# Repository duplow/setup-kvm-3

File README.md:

# setup-kvm-3

**Chaveador KVM** (**K**eyboard **V**ideo **M**ouse) para até 3 PCs/aparelhos diferentes conectados simultaneamente, podendo alternar entre sí.

_Imagem ilustrativa_

Cada aparelho conectado contará com 3 entradas **HDMI**, 3 entradas **DisplayPort** e 1 entrada **USB 3.0**.

O projeto é montado em cima de um Arduino para fazer o chaveamento entre os aparelhos via teclado, caso opte por um chaveamento apenas via botão fisico o Arduino não será necessário.

O chavemento será feito pelo botão físico no aparelho ou via um teclado USB usando os atalhos:

- `CTRL+SHIFT+NUM+1` para o aparelho número 1
- `CTRL+SHIFT+NUM+2` para o aparelho número 2
- `CTRL+SHIFT+NUM+3` para o aparelho número 3

e assim por diante

---

## Instruções

### Fabricação

 - espessura minima das trilhas (width): 0.2mm
 - espaçamento minimo (min clearance): 0.2mm (usado 0.25m)
 - fotolito: 10.000 DPI

### Módulos

- [Módulo Alimentação](/docs/power-module.md)
- [Módulo Displayport](/docs/displayport-module.md)
- [Módulo USB 3.0 tipo A](/docs/usb-30-module.md)
- [Módulo Controle](/docs/controller-module.md)

### Materiais

Componentes necessários para um KVM de até 3 aparelhos:

- **Arduino** qualquer modelo (opcional)
- 70x Buffers **SN74HC541N** (6 por HDMI, 6 por DisplayPort e 2 por USB)
- 4x Conectores **USB 3.0 DIP** fêmea
- 9x Conectores **HDMI** fêmea [link de venda](https://pt.aliexpress.com/item/1005004321901753.html?spm=a2g0o.productlist.main.3.2f4c4bd4zNbfgg&algo_pvid=e8ba0e93-4177-44cf-a99c-585d2ebb48c4&aem_p4p_detail=202302081917461309186084719520000121513&algo_exp_id=e8ba0e93-4177-44cf-a99c-585d2ebb48c4-1&pdp_ext_f=%7B%22sku_id%22%3A%2212000028751193682%22%7D&pdp_npi=3%40dis%21BRL%2118.99%2116.71%21%21%21%21%21%40211bf48d16759126661676453d06b6%2112000028751193682%21sea%21BR%214164761864&curPageLogUid=yP8cfGhjvAHO&ad_pvid=202302081917461309186084719520000121513_2&ad_pvid=202302081917461309186084719520000121513_2)
- 9x Conectores **DisplayPort DIP** fêmea
- 4x Conectores **P2** de áudio e microfone [link de venda](https://pt.aliexpress.com/item/1005004688929020.html?spm=a2g0o.ppclist.product.16.73faLsI4LsI4iQ&pdp_npi=2%40dis%21BRL%21R%24%205%2C92%21R%24%205%2C92%21%21%21%21%21%402101f6b316766497700243772e69af%2112000030107125153%21btf&_t=pvid%3Ad92d09f6-7fa5-46f7-80e0-bc18aa72a762&afTraceInfo=1005004688929020__pc__pcBridgePPC__xxxxxx__1676649770&gatewayAdapt=glo2bra)

> É possível substituir os buffers `SN74HC541N` por multiplexadores `74HC4052`, porém será necessário muitos deles para fazer o mesmo trabalho, para cada `SN74HC541N` será necessário mais ou menos 4 multiplexadores `74HC4052`.

TODO: Colocar o link para o BOM

### Esquemas

Placa USB

### Montagem

Em desenvolvimento

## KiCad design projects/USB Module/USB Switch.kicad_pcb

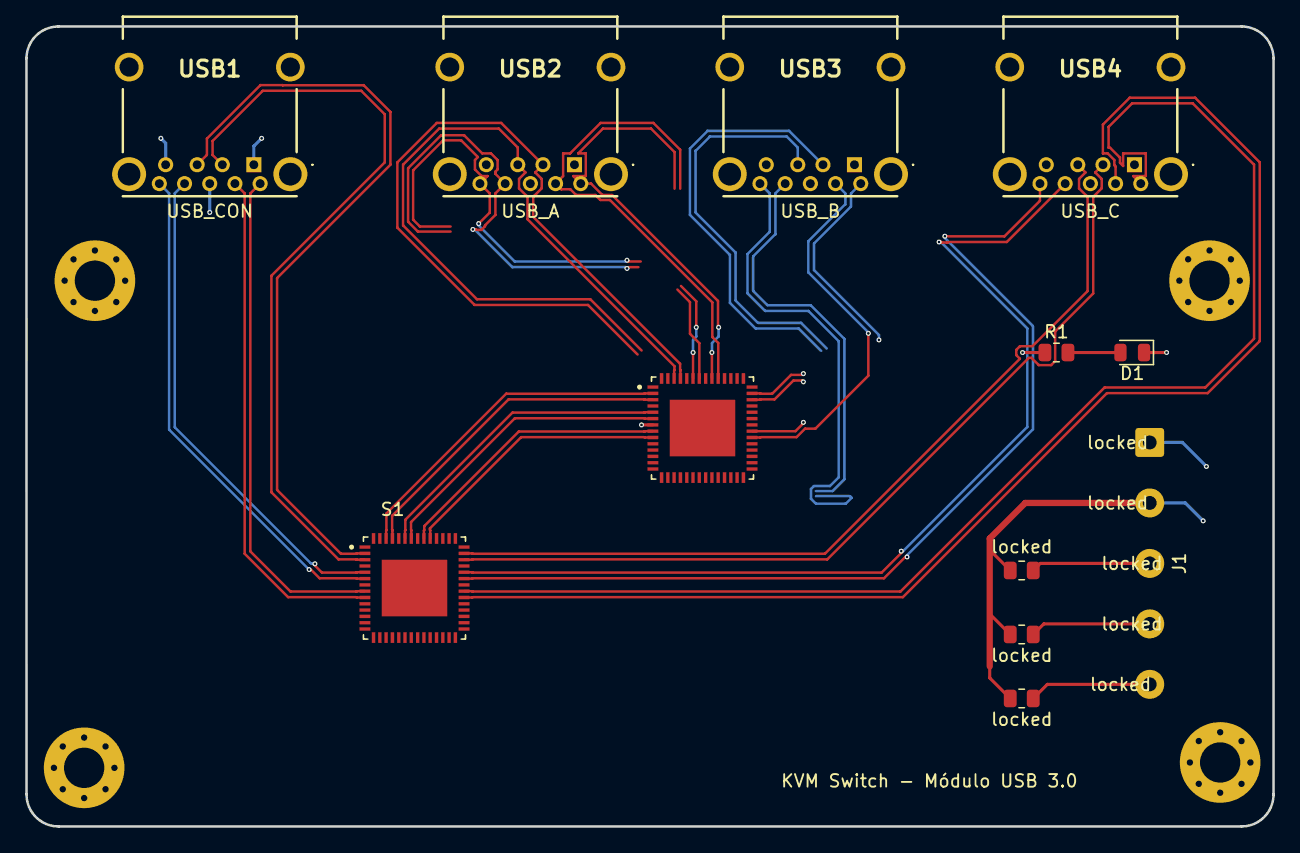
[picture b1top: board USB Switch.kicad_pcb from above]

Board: 4 copper layers, 99.0 x 63.5 mm, 12 parts (0 on the bottom side), 38 nets.

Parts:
D1: LED; LED_0805_2012Metric
J1: Conn_01x05_Socket; SolderWire-0.5sqmm_1x05_P4.8mm_D0.9mm_OD2.3mm
R1: 167R; R_0805_2012Metric
S1, S2: HD3SS215IRTQR; QFN50P800X800X100-57N
USB1, USB2, USB3, USB4: USB3_Molex_48393-0003
locked: locked; R_0805_2012Metric
locked#2, locked#3: locked; R_0805_2012Metric

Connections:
/+5V: J1.1, R1.1
/CLOCK: J1.5, locked#2.1
/GND: D1.1 (K), J1.2, locked.2, locked#2.2, locked#3.2
/S0: J1.3, S2.1 (AUX_SEL), S2.56 (DX_SEL), locked#3.1
/S1: J1.4, S1.1 (AUX_SEL), S1.56 (DX_SEL), locked.1
/Switch/+5V: S1.19 (VDD0), S1.43 (OE), S1.55 (VDD1), S2.19 (VDD0), S2.43 (OE), S2.55 (VDD1), USB1.1 (VBUS)
/Switch/D0+: S1.2 (D0_C+), USB1.3 (D+)
/Switch/D0-: S1.3 (D0_C-), USB1.2 (D-)
/Switch/D1+: S1.5 (D1_C+), USB1.6 (SSRX+)
/Switch/D1-: S1.6 (D1_C-), USB1.5 (SSRX-)
/Switch/D2+: S1.8 (D2_C+), USB1.9 (SSTX+)
/Switch/D2-: S1.9 (D2_C-), USB1.8 (SSTX-)
/Switch/USB_AB_D0+: S1.54 (D0_A+), S2.2 (D0_C+)
/Switch/USB_AB_D0-: S1.53 (D0_A-), S2.3 (D0_C-)
/Switch/USB_AB_D1+: S1.51 (D1_A+), S2.5 (D1_C+)
/Switch/USB_AB_D1-: S1.50 (D1_A-), S2.6 (D1_C-)
/Switch/USB_AB_D2+: S1.48 (D2_A+), S2.8 (D2_C+)
/Switch/USB_AB_D2-: S1.47 (D2_A-), S2.9 (D2_C-)
/Switch/USB_A_D0+: S2.54 (D0_A+), USB2.3 (D+)
/Switch/USB_A_D0-: S2.53 (D0_A-), USB2.2 (D-)
/Switch/USB_A_D1+: S2.51 (D1_A+), USB2.6 (SSRX+)
/Switch/USB_A_D1-: S2.50 (D1_A-), USB2.5 (SSRX-)
/Switch/USB_A_D2+: S2.48 (D2_A+), USB2.9 (SSTX+)
/Switch/USB_A_D2-: S2.47 (D2_A-), USB2.8 (SSTX-)
/Switch/USB_B_D0+: S2.41 (D0_B+), USB3.3 (D+)
/Switch/USB_B_D0-: S2.40 (D0_B-), USB3.2 (D-)
/Switch/USB_B_D1+: S2.38 (D1_B+), USB3.6 (SSRX+)
/Switch/USB_B_D1-: S2.37 (D1_B-), USB3.5 (SSRX-)
/Switch/USB_B_D2+: S2.35 (D2_B+), USB3.9 (SSTX+)
/Switch/USB_B_D2-: S2.34 (D2_B-), USB3.8 (SSTX-)
/Switch/USB_C_D0+: S1.41 (D0_B+), USB4.3 (D+)
/Switch/USB_C_D0-: S1.40 (D0_B-), USB4.2 (D-)
/Switch/USB_C_D1+: S1.38 (D1_B+), USB4.6 (SSRX+)
/Switch/USB_C_D1-: S1.37 (D1_B-), USB4.5 (SSRX-)
/Switch/USB_C_D2+: S1.35 (D2_B+), USB4.9 (SSTX+)
/Switch/USB_C_D2-: S1.34 (D2_B-), USB4.8 (SSTX-)
GND: S1.4 (GND0), S1.7 (GND1), S1.10 (GND2), S1.33 (GND3), S1.36 (GND4), S1.39 (GND5), S1.46 (GND6), S1.49 (GND7), S1.52 (GND8), S1.57 (PAD), S2.4 (GND0), S2.7 (GND1), S2.10 (GND2), S2.33 (GND3), S2.36 (GND4), S2.39 (GND5), S2.46 (GND6), S2.49 (GND7), S2.52 (GND8), S2.57 (PAD), USB1.4 (GND), USB1.7 (GND_DRAIN)
unnamed: D1.2 (A), R1.2

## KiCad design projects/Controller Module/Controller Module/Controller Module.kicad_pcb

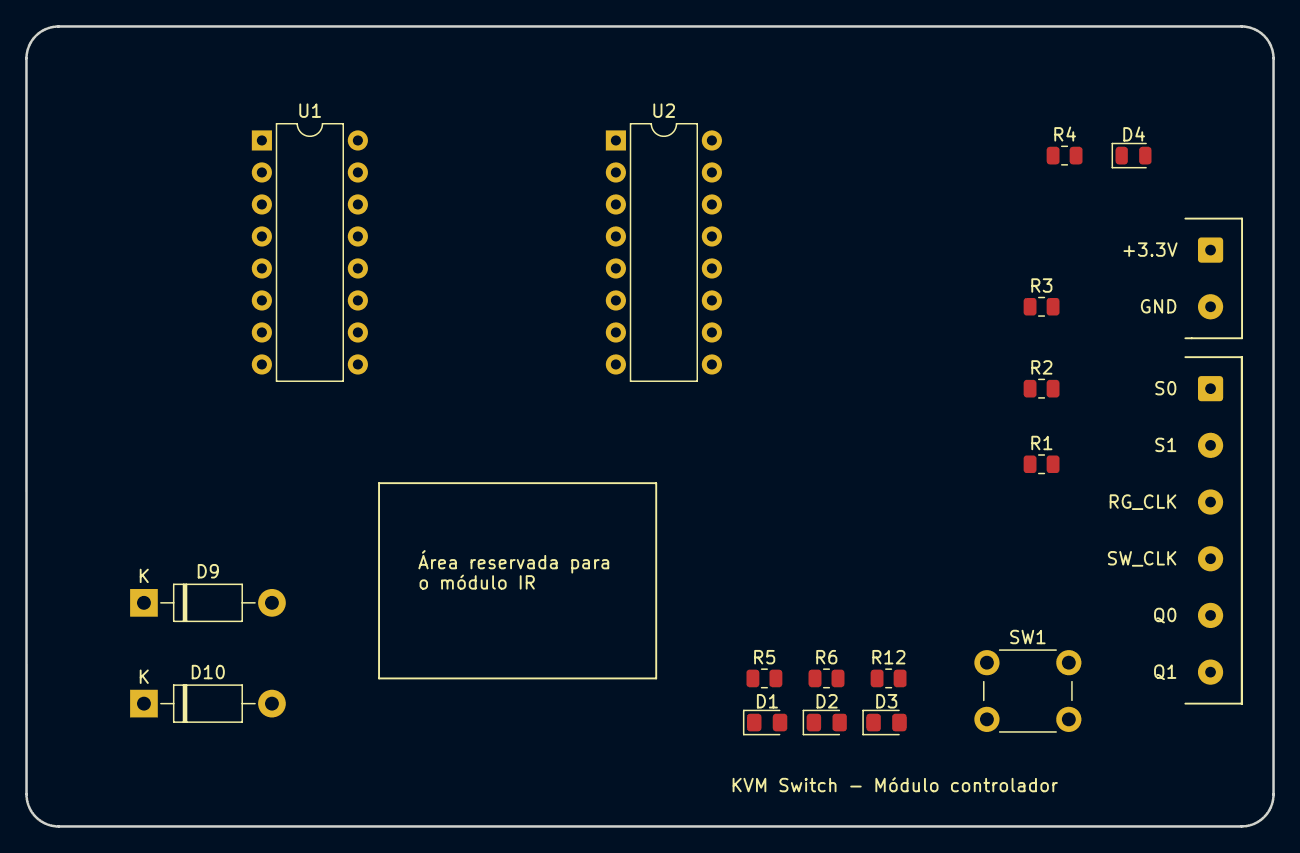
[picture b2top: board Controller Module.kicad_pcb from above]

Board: 2 copper layers, 99.0 x 63.5 mm, 18 parts (0 on the bottom side), 14 nets, no tracks yet.

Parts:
D1: LED1; LED_0805_2012Metric_Pad1.15x1.40mm_HandSolder
D2: LED2; LED_0805_2012Metric_Pad1.15x1.40mm_HandSolder
D3: LED3; LED_0805_2012Metric_Pad1.15x1.40mm_HandSolder
D4: LED; LED_0805_2012Metric
D9, D10: 1N4001; D_DO-41_SOD81_P10.16mm_Horizontal
J1: Conn_01x02_Socket; SolderWire-0.25sqmm_1x02_P4.5mm_D0.65mm_OD2mm
J2: Conn_01x06_Socket; SolderWire-0.25sqmm_1x06_P4.5mm_D0.65mm_OD2mm
R1, R2, R3: 10k; R_0805_2012Metric
R4: 75R; R_0805_2012Metric
R5, R6, R12: R75; R_0805_2012Metric
SW1: SW_DIP_x01; SW_PUSH_6mm
U1: 4017; DIP-16_W7.62mm
U2: 74LS195; DIP-16_W7.62mm

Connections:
+3.3V: J1.1, R4.1, SW1.1, U1.16 (VDD), U2.16 (VCC)
/Control Sheet/LED2_ON: D9.1 (K), R6.1, U1.2 (Q1), U2.4 (P0)
/Control Sheet/LED3_ON: D10.1 (K), R12.1, U1.4 (Q2), U2.5 (P1)
/Control Sheet/REG_CLK: J2.3, J2.4, SW1.2, U1.14 (CLK), U2.10 (CP)
/Control Sheet/RESET: U1.7 (Q3), U1.15 (Reset)
/Control Sheet/SI0: D9.2 (A), J2.1
/Control Sheet/SI1: D10.2 (A), J2.2
/Control Sheet/SO0: J2.5, U2.15 (Q0)
/Control Sheet/SO1: J2.6, U2.14 (Q1)
GND: D1.1 (K), D2.1 (K), D3.1 (K), D4.1 (K), J1.2, R1.2, R2.2, R3.2, U1.8 (VSS), U2.8 (GND)
unnamed: D1.2 (A), R5.2
unnamed: D2.2 (A), R6.2
unnamed: D3.2 (A), R12.2
unnamed: D4.2 (A), R4.2

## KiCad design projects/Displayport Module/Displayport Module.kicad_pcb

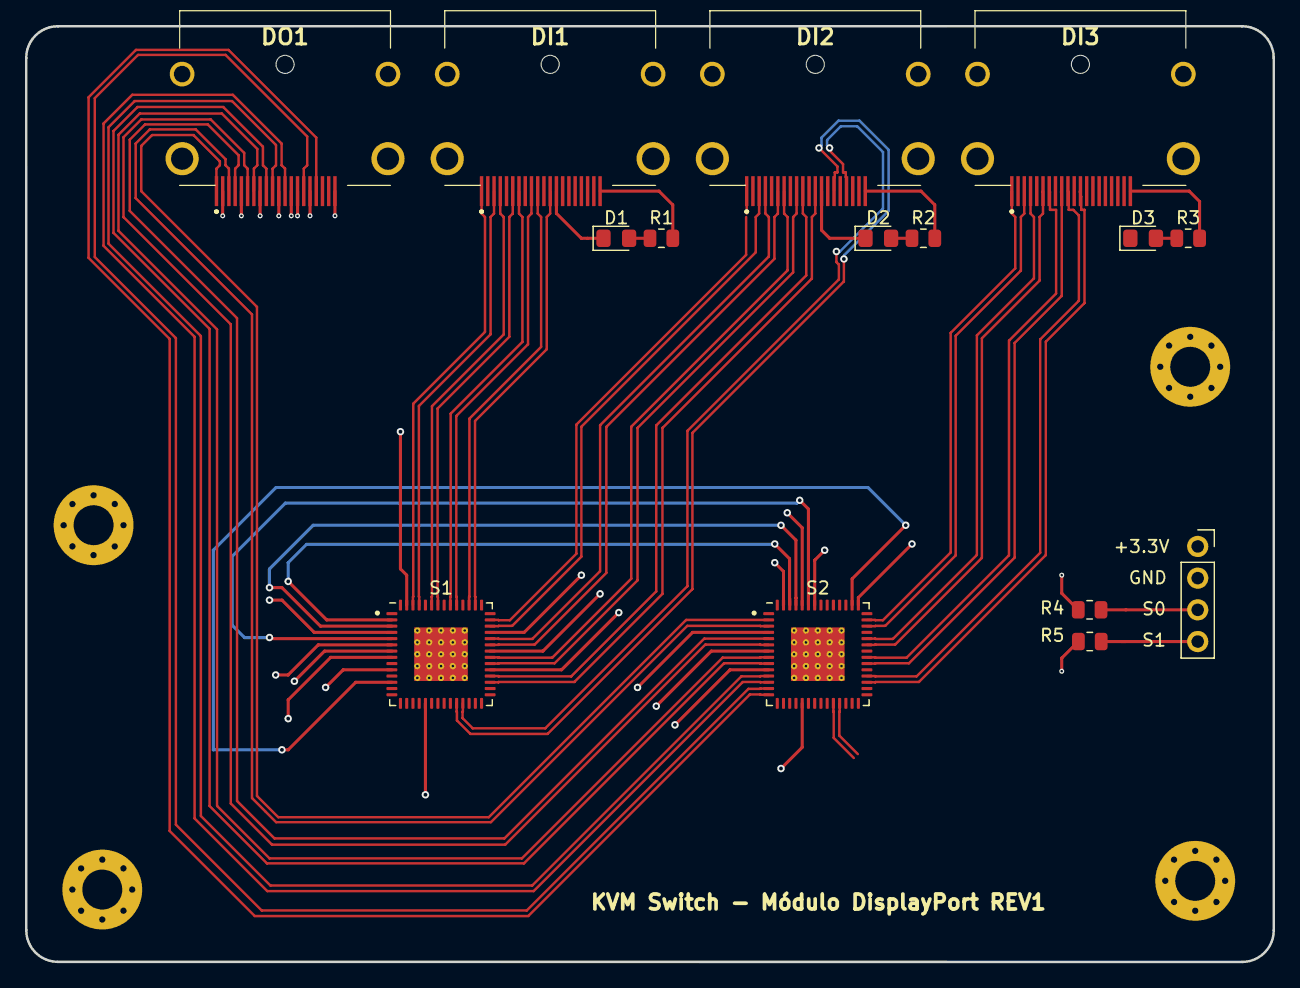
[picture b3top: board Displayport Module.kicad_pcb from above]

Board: 4 copper layers, 100.0 x 75.0 mm, 14 parts (0 on the bottom side), 68 nets.

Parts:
D1, D2, D3: LED; LED_0805_2012Metric_Pad1.15x1.40mm_HandSolder
DI1, DI2, DI3: Connector DP IN 47272-0024; 47272-0024
DO1: Connector DP OUT 47272-0024; 47272-0024
R1, R2, R3: R75; R_0805_2012Metric
R4, R5: 10K; R_0805_2012Metric
S1, S2: HD3SS215IRTQR; QFN-56-1EP_8x8mm_P0.5mm_EP4.3x4.3mm_ThermalVias

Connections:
+3.3V: DO1.20 (PWR), S1.19 (VDD0), S1.43 (OE), S1.55 (VDD1), S2.19 (VDD0), S2.43 (OE), S2.55 (VDD1)
/DPIN1_AUX+: DI1.15 (AUX+), S1.30 (AUX_A+)
/DPIN1_AUX-: DI1.17 (AUX-), S1.29 (AUX_A-)
/DPIN1_D0+: DI1.1 (D0+), S1.54 (D0_A+)
/DPIN1_D0-: DI1.3 (D0-), S1.53 (D0_A-)
/DPIN1_D1+: DI1.4 (D1+), S1.51 (D1_A+)
/DPIN1_D1-: DI1.6 (D1-), S1.50 (D1_A-)
/DPIN1_D2+: DI1.7 (D2+), S1.48 (D2_A+)
/DPIN1_D2-: DI1.9 (D2-), S1.47 (D2_A-)
/DPIN1_D3+: DI1.10 (D3+), S1.45 (D3_A+)
/DPIN1_D3-: DI1.12 (D3-), S1.44 (D3_A-)
/DPIN1_GND: D1.1 (K), DI1.13 (CON1)
/DPIN1_HPD: DI1.18 (HPD), S1.16 (HPD_A)
/DPIN1_PWR: DI1.20 (PWR), R1.1
/DPIN2_AUX+: DI2.15 (AUX+), S1.24 (AUX_B+)
/DPIN2_AUX-: DI2.17 (AUX-), S1.25 (AUX_B-)
/DPIN2_D0+: DI2.1 (D0+), S1.41 (D0_B+)
/DPIN2_D0-: DI2.3 (D0-), S1.40 (D0_B-)
/DPIN2_D1+: DI2.4 (D1+), S1.38 (D1_B+)
/DPIN2_D1-: DI2.6 (D1-), S1.37 (D1_B-)
/DPIN2_D2+: DI2.7 (D2+), S1.35 (D2_B+)
/DPIN2_D2-: DI2.9 (D2-), S1.34 (D2_B-)
/DPIN2_D3+: DI2.10 (D3+), S1.32 (D3_B+)
/DPIN2_D3-: DI2.12 (D3-), S1.31 (D3_B-)
/DPIN2_GND: D2.1 (K), DI2.13 (CON1)
/DPIN2_HPD: DI2.18 (HPD), S1.17 (HPD_B)
/DPIN2_PWR: DI2.20 (PWR), R2.1
/DPIN3_AUX+: DI3.15 (AUX+), S2.24 (AUX_B+)
/DPIN3_AUX-: DI3.17 (AUX-), S2.25 (AUX_B-)
/DPIN3_D0+: DI3.1 (D0+), S2.41 (D0_B+)
/DPIN3_D0-: DI3.3 (D0-), S2.40 (D0_B-)
/DPIN3_D1+: DI3.4 (D1+), S2.38 (D1_B+)
/DPIN3_D1-: DI3.6 (D1-), S2.37 (D1_B-)
/DPIN3_D2+: DI3.7 (D2+), S2.35 (D2_B+)
/DPIN3_D2-: DI3.9 (D2-), S2.34 (D2_B-)
/DPIN3_D3+: DI3.10 (D3+), S2.32 (D3_B+)
/DPIN3_D3-: DI3.12 (D3-), S2.31 (D3_B-)
/DPIN3_GND: D3.1 (K), DI3.13 (CON1)
/DPIN3_HPD: DI3.18 (HPD), S2.17 (HPD_B)
/DPIN3_PWR: DI3.20 (PWR), R3.1
/DPOUT_AUX+: DO1.15 (AUX+), S2.13 (AUX_C+)
/DPOUT_AUX-: DO1.17 (AUX-), S2.14 (AUX_C-)
/DPOUT_D0+: DO1.1 (D0+), S2.2 (D0_C+)
/DPOUT_D0-: DO1.3 (D0-), S2.3 (D0_C-)
/DPOUT_D1+: DO1.4 (D1+), S2.5 (D1_C+)
/DPOUT_D1-: DO1.6 (D1-), S2.6 (D1_C-)
/DPOUT_D2+: DO1.7 (D2+), S2.8 (D2_C+)
/DPOUT_D2-: DO1.9 (D2-), S2.9 (D2_C-)
/DPOUT_D3+: DO1.10 (D3+), S2.11 (D3_C+)
/DPOUT_D3-: DO1.12 (D3-), S2.12 (D3_C-)
/DPOUT_HPD: DO1.18 (HPD), S2.15 (HPD_C)
/S0: R4.1, S1.1 (AUX_SEL), S1.56 (DX_SEL)
/S1: R5.1, S2.1 (AUX_SEL), S2.56 (DX_SEL)
GND: DO1.2 (GND0), DO1.5 (GND1), DO1.8 (GND2), DO1.11 (GND3), DO1.13 (CON1), DO1.14 (CON2), DO1.16 (GND4), R4.2, R5.2, S1.4 (GND0), S1.7 (GND1), S1.10 (GND2), S1.33 (GND3), S1.36 (GND4), S1.39 (GND5), S1.46 (GND6), S1.49 (GND7), S1.52 (GND8), S2.4 (GND0), S2.7 (GND1), S2.10 (GND2), S2.33 (GND3), S2.36 (GND4), S2.39 (GND5), S2.46 (GND6), S2.49 (GND7), S2.52 (GND8)
unnamed: D1.2 (A), R1.2
unnamed: D2.2 (A), R2.2
unnamed: D3.2 (A), R3.2
unnamed: S1.13 (AUX_C+), S2.30 (AUX_A+)
unnamed: S1.14 (AUX_C-), S2.29 (AUX_A-)
unnamed: S1.2 (D0_C+), S2.54 (D0_A+)
unnamed: S1.3 (D0_C-), S2.53 (D0_A-)
unnamed: S1.5 (D1_C+), S2.51 (D1_A+)
unnamed: S1.6 (D1_C-), S2.50 (D1_A-)
unnamed: S1.8 (D2_C+), S2.48 (D2_A+)
unnamed: S1.9 (D2_C-), S2.47 (D2_A-)
unnamed: S1.11 (D3_C+), S2.45 (D3_A+)
unnamed: S1.12 (D3_C-), S2.44 (D3_A-)
unnamed: S1.15 (HPD_C), S2.16 (HPD_A)

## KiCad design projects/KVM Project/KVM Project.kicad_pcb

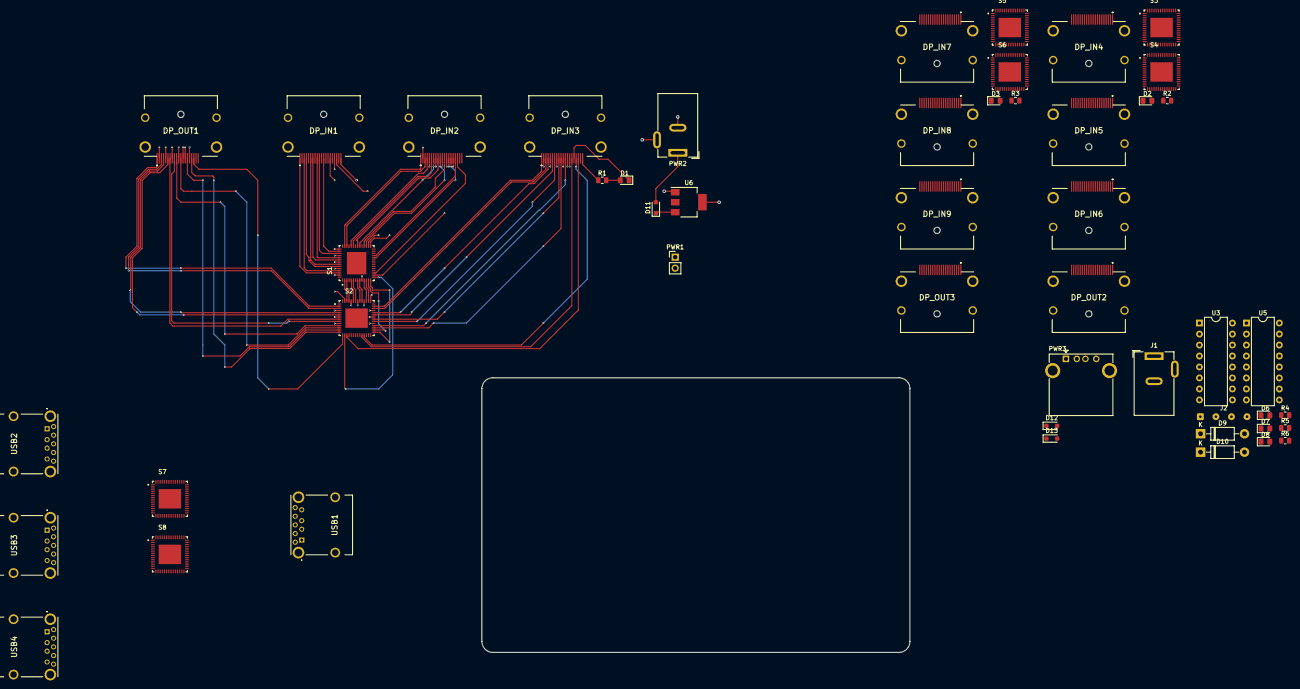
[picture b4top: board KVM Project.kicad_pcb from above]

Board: 4 copper layers, 49 parts (0 on the bottom side), 221 nets.

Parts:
D1, D2, D3: LED; LED_0805_2012Metric_Pad1.15x1.40mm_HandSolder
D6: LED1; LED_0805_2012Metric_Pad1.15x1.40mm_HandSolder
D7: LED2; LED_0805_2012Metric_Pad1.15x1.40mm_HandSolder
D8: LED3; LED_0805_2012Metric_Pad1.15x1.40mm_HandSolder
D9, D10: 1N4001; D_DO-41_SOD81_P10.16mm_Horizontal
D11, D12, D13: 1N5819WS; D_SOD-323_HandSoldering
DP_IN1, DP_IN4, DP_IN7: DP_IN1; 472720024
DP_IN2, DP_IN5, DP_IN8: DP_IN2; 472720024
DP_IN3, DP_IN6, DP_IN9: DP_IN3; 472720024
DP_OUT1, DP_OUT2, DP_OUT3: DP_OUT; 472720024
J1: Barrel_Jack_Switch; BarrelJack_Wuerth_6941xx301002
J2: IO pins; SolderWire-0.1sqmm_1x04_P3.6mm_D0.4mm_OD1mm
PWR1: Conn_01x02_Pin; PinHeader_1x02_P2.54mm_Vertical
PWR2: Barrel_Jack_Switch; BarrelJack_Wuerth_6941xx301002
PWR3: USB_A; USB_A_CONNFLY_DS1095-WNR0
R1, R2, R3, R4, R5, R6: R75; R_0805_2012Metric
S1, S2, S3, S4, S5, S6, S7, S8: HD3SS215IRTQR; QFN50P800X800X100-57N
U3: 4017; DIP-16_W7.62mm
U5: 74LS195; DIP-16_W7.62mm
U6: AMS1117-3.3; SOT-223-3_TabPin2
USB1, USB2, USB3, USB4: USB3_Molex_48393-0003

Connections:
+3.3V: DP_IN1.20 (PWR), DP_IN2.20 (PWR), DP_IN4.20 (PWR), DP_IN5.20 (PWR), DP_IN7.20 (PWR), DP_IN8.20 (PWR), DP_OUT1.20 (PWR), DP_OUT2.20 (PWR), DP_OUT3.20 (PWR), J1.1, S1.19 (VDD0), S1.43 (OE), S1.55 (VDD1), S2.19 (VDD0), S2.43 (OE), S2.55 (VDD1), S3.19 (VDD0), S3.43 (OE), S3.55 (VDD1), S4.19 (VDD0), S4.43 (OE), S4.55 (VDD1), S5.19 (VDD0), S5.43 (OE), S5.55 (VDD1), S6.19 (VDD0), S6.43 (OE), S6.55 (VDD1), U3.16 (VDD), U5.16 (VCC), U6.2 (VO)
/Control/LED2_ON: D9.1 (K), R5.1, U3.2 (Q1), U5.4 (P0)
/Control/LED3_ON: D10.1 (K), R6.1, U3.4 (Q2), U5.5 (P1)
/Control/REG_CLK: J2.3, J2.4, U3.14 (CLK), U5.10 (CP)
/Control/RESET: U3.7 (Q3), U3.15 (Reset)
/Control/SI0: D9.2 (A), J2.1
/Control/SI1: D10.2 (A), J2.2
/Display_1/DPIN1_AUX+: DP_IN1.15 (AUX+), S1.30 (AUX_A+)
/Display_1/DPIN1_AUX-: DP_IN1.17 (AUX-), S1.29 (AUX_A-)
/Display_1/DPIN1_D0+: DP_IN1.1 (D0+), S1.54 (D0_A+)
/Display_1/DPIN1_D0-: DP_IN1.3 (D0-), S1.53 (D0_A-)
/Display_1/DPIN1_D1+: DP_IN1.4 (D1+), S1.51 (D1_A+)
/Display_1/DPIN1_D1-: DP_IN1.6 (D1-), S1.50 (D1_A-)
/Display_1/DPIN1_D2+: DP_IN1.7 (D2+), S1.48 (D2_A+)
/Display_1/DPIN1_D2-: DP_IN1.9 (D2-), S1.47 (D2_A-)
/Display_1/DPIN1_D3+: DP_IN1.10 (D3+), S1.45 (D3_A+)
/Display_1/DPIN1_D3-: DP_IN1.12 (D3-), S1.44 (D3_A-)
/Display_1/DPIN1_HPD: DP_IN1.18 (HPD), S1.16 (HPD_A)
/Display_1/DPIN2_AUX+: DP_IN2.15 (AUX+), S1.24 (AUX_B+)
/Display_1/DPIN2_AUX-: DP_IN2.17 (AUX-), S1.25 (AUX_B-)
/Display_1/DPIN2_D0+: DP_IN2.1 (D0+), S1.41 (D0_B+)
/Display_1/DPIN2_D0-: DP_IN2.3 (D0-), S1.40 (D0_B-)
/Display_1/DPIN2_D1+: DP_IN2.4 (D1+), S1.38 (D1_B+)
/Display_1/DPIN2_D1-: DP_IN2.6 (D1-), S1.37 (D1_B-)
/Display_1/DPIN2_D2+: DP_IN2.7 (D2+), S1.35 (D2_B+)
/Display_1/DPIN2_D2-: DP_IN2.9 (D2-), S1.34 (D2_B-)
/Display_1/DPIN2_D3+: DP_IN2.10 (D3+), S1.32 (D3_B+)
/Display_1/DPIN2_D3-: DP_IN2.12 (D3-), S1.31 (D3_B-)
/Display_1/DPIN2_HPD: DP_IN2.18 (HPD), S1.17 (HPD_B)
/Display_1/DPIN3_AUX+: DP_IN3.15 (AUX+), S2.24 (AUX_B+)
/Display_1/DPIN3_AUX-: DP_IN3.17 (AUX-), S2.25 (AUX_B-)
/Display_1/DPIN3_D0+: DP_IN3.1 (D0+), S2.41 (D0_B+)
/Display_1/DPIN3_D0-: DP_IN3.3 (D0-), S2.40 (D0_B-)
/Display_1/DPIN3_D1+: DP_IN3.4 (D1+), S2.38 (D1_B+)
/Display_1/DPIN3_D1-: DP_IN3.6 (D1-), S2.37 (D1_B-)
/Display_1/DPIN3_D2+: DP_IN3.7 (D2+), S2.35 (D2_B+)
/Display_1/DPIN3_D2-: DP_IN3.9 (D2-), S2.34 (D2_B-)
/Display_1/DPIN3_D3+: DP_IN3.10 (D3+), S2.32 (D3_B+)
/Display_1/DPIN3_D3-: DP_IN3.12 (D3-), S2.31 (D3_B-)
/Display_1/DPIN3_GND: D1.1 (K), DP_IN3.16 (GND4)
/Display_1/DPIN3_HPD: DP_IN3.18 (HPD), S2.17 (HPD_B)
/Display_1/DPIN3_PWR: DP_IN3.20 (PWR), R1.1
/Display_1/DPOUT_AUX+: DP_OUT1.15 (AUX+), S2.13 (AUX_C+)
/Display_1/DPOUT_AUX-: DP_OUT1.17 (AUX-), S2.14 (AUX_C-)
/Display_1/DPOUT_D0+: DP_OUT1.1 (D0+), S2.2 (D0_C+)
/Display_1/DPOUT_D0-: DP_OUT1.3 (D0-), S2.3 (D0_C-)
/Display_1/DPOUT_D1+: DP_OUT1.4 (D1+), S2.5 (D1_C+)
/Display_1/DPOUT_D1-: DP_OUT1.6 (D1-), S2.6 (D1_C-)
/Display_1/DPOUT_D2+: DP_OUT1.7 (D2+), S2.8 (D2_C+)
/Display_1/DPOUT_D2-: DP_OUT1.9 (D2-), S2.9 (D2_C-)
/Display_1/DPOUT_D3+: DP_OUT1.10 (D3+), S2.11 (D3_C+)
/Display_1/DPOUT_D3-: DP_OUT1.12 (D3-), S2.12 (D3_C-)
/Display_1/DPOUT_HPD: DP_OUT1.18 (HPD), S2.15 (HPD_C)
/Display_2/DPIN1_AUX+: DP_IN4.15 (AUX+), S3.30 (AUX_A+)
/Display_2/DPIN1_AUX-: DP_IN4.17 (AUX-), S3.29 (AUX_A-)
/Display_2/DPIN1_D0+: DP_IN4.1 (D0+), S3.54 (D0_A+)
/Display_2/DPIN1_D0-: DP_IN4.3 (D0-), S3.53 (D0_A-)
/Display_2/DPIN1_D1+: DP_IN4.4 (D1+), S3.51 (D1_A+)
/Display_2/DPIN1_D1-: DP_IN4.6 (D1-), S3.50 (D1_A-)
/Display_2/DPIN1_D2+: DP_IN4.7 (D2+), S3.48 (D2_A+)
/Display_2/DPIN1_D2-: DP_IN4.9 (D2-), S3.47 (D2_A-)
/Display_2/DPIN1_D3+: DP_IN4.10 (D3+), S3.45 (D3_A+)
/Display_2/DPIN1_D3-: DP_IN4.12 (D3-), S3.44 (D3_A-)
/Display_2/DPIN1_HPD: DP_IN4.18 (HPD), S3.16 (HPD_A)
/Display_2/DPIN2_AUX+: DP_IN5.15 (AUX+), S3.24 (AUX_B+)
/Display_2/DPIN2_AUX-: DP_IN5.17 (AUX-), S3.25 (AUX_B-)
/Display_2/DPIN2_D0+: DP_IN5.1 (D0+), S3.41 (D0_B+)
/Display_2/DPIN2_D0-: DP_IN5.3 (D0-), S3.40 (D0_B-)
/Display_2/DPIN2_D1+: DP_IN5.4 (D1+), S3.38 (D1_B+)
/Display_2/DPIN2_D1-: DP_IN5.6 (D1-), S3.37 (D1_B-)
/Display_2/DPIN2_D2+: DP_IN5.7 (D2+), S3.35 (D2_B+)
/Display_2/DPIN2_D2-: DP_IN5.9 (D2-), S3.34 (D2_B-)
/Display_2/DPIN2_D3+: DP_IN5.10 (D3+), S3.32 (D3_B+)
/Display_2/DPIN2_D3-: DP_IN5.12 (D3-), S3.31 (D3_B-)
/Display_2/DPIN2_HPD: DP_IN5.18 (HPD), S3.17 (HPD_B)
/Display_2/DPIN3_AUX+: DP_IN6.15 (AUX+), S4.24 (AUX_B+)
/Display_2/DPIN3_AUX-: DP_IN6.17 (AUX-), S4.25 (AUX_B-)
/Display_2/DPIN3_D0+: DP_IN6.1 (D0+), S4.41 (D0_B+)
/Display_2/DPIN3_D0-: DP_IN6.3 (D0-), S4.40 (D0_B-)
/Display_2/DPIN3_D1+: DP_IN6.4 (D1+), S4.38 (D1_B+)
/Display_2/DPIN3_D1-: DP_IN6.6 (D1-), S4.37 (D1_B-)
/Display_2/DPIN3_D2+: DP_IN6.7 (D2+), S4.35 (D2_B+)
/Display_2/DPIN3_D2-: DP_IN6.9 (D2-), S4.34 (D2_B-)
/Display_2/DPIN3_D3+: DP_IN6.10 (D3+), S4.32 (D3_B+)
/Display_2/DPIN3_D3-: DP_IN6.12 (D3-), S4.31 (D3_B-)
/Display_2/DPIN3_GND: D2.1 (K), DP_IN6.16 (GND4)
/Display_2/DPIN3_HPD: DP_IN6.18 (HPD), S4.17 (HPD_B)
/Display_2/DPIN3_PWR: DP_IN6.20 (PWR), R2.1
/Display_2/DPOUT_AUX+: DP_OUT2.15 (AUX+), S4.13 (AUX_C+)
/Display_2/DPOUT_AUX-: DP_OUT2.17 (AUX-), S4.14 (AUX_C-)
/Display_2/DPOUT_D0+: DP_OUT2.1 (D0+), S4.2 (D0_C+)
/Display_2/DPOUT_D0-: DP_OUT2.3 (D0-), S4.3 (D0_C-)
/Display_2/DPOUT_D1+: DP_OUT2.4 (D1+), S4.5 (D1_C+)
/Display_2/DPOUT_D1-: DP_OUT2.6 (D1-), S4.6 (D1_C-)
/Display_2/DPOUT_D2+: DP_OUT2.7 (D2+), S4.8 (D2_C+)
/Display_2/DPOUT_D2-: DP_OUT2.9 (D2-), S4.9 (D2_C-)
/Display_2/DPOUT_D3+: DP_OUT2.10 (D3+), S4.11 (D3_C+)
/Display_2/DPOUT_D3-: DP_OUT2.12 (D3-), S4.12 (D3_C-)
/Display_2/DPOUT_HPD: DP_OUT2.18 (HPD), S4.15 (HPD_C)
/Display_3/DPIN1_AUX+: DP_IN7.15 (AUX+), S5.30 (AUX_A+)
/Display_3/DPIN1_AUX-: DP_IN7.17 (AUX-), S5.29 (AUX_A-)
/Display_3/DPIN1_D0+: DP_IN7.1 (D0+), S5.54 (D0_A+)
/Display_3/DPIN1_D0-: DP_IN7.3 (D0-), S5.53 (D0_A-)
/Display_3/DPIN1_D1+: DP_IN7.4 (D1+), S5.51 (D1_A+)
/Display_3/DPIN1_D1-: DP_IN7.6 (D1-), S5.50 (D1_A-)
/Display_3/DPIN1_D2+: DP_IN7.7 (D2+), S5.48 (D2_A+)
/Display_3/DPIN1_D2-: DP_IN7.9 (D2-), S5.47 (D2_A-)
/Display_3/DPIN1_D3+: DP_IN7.10 (D3+), S5.45 (D3_A+)
/Display_3/DPIN1_D3-: DP_IN7.12 (D3-), S5.44 (D3_A-)
/Display_3/DPIN1_HPD: DP_IN7.18 (HPD), S5.16 (HPD_A)
/Display_3/DPIN2_AUX+: DP_IN8.15 (AUX+), S5.24 (AUX_B+)
/Display_3/DPIN2_AUX-: DP_IN8.17 (AUX-), S5.25 (AUX_B-)
/Display_3/DPIN2_D0+: DP_IN8.1 (D0+), S5.41 (D0_B+)
/Display_3/DPIN2_D0-: DP_IN8.3 (D0-), S5.40 (D0_B-)
/Display_3/DPIN2_D1+: DP_IN8.4 (D1+), S5.38 (D1_B+)
/Display_3/DPIN2_D1-: DP_IN8.6 (D1-), S5.37 (D1_B-)
/Display_3/DPIN2_D2+: DP_IN8.7 (D2+), S5.35 (D2_B+)
/Display_3/DPIN2_D2-: DP_IN8.9 (D2-), S5.34 (D2_B-)
/Display_3/DPIN2_D3+: DP_IN8.10 (D3+), S5.32 (D3_B+)
/Display_3/DPIN2_D3-: DP_IN8.12 (D3-), S5.31 (D3_B-)
/Display_3/DPIN2_HPD: DP_IN8.18 (HPD), S5.17 (HPD_B)
/Display_3/DPIN3_AUX+: DP_IN9.15 (AUX+), S6.24 (AUX_B+)
/Display_3/DPIN3_AUX-: DP_IN9.17 (AUX-), S6.25 (AUX_B-)
/Display_3/DPIN3_D0+: DP_IN9.1 (D0+), S6.41 (D0_B+)
/Display_3/DPIN3_D0-: DP_IN9.3 (D0-), S6.40 (D0_B-)
/Display_3/DPIN3_D1+: DP_IN9.4 (D1+), S6.38 (D1_B+)
/Display_3/DPIN3_D1-: DP_IN9.6 (D1-), S6.37 (D1_B-)
/Display_3/DPIN3_D2+: DP_IN9.7 (D2+), S6.35 (D2_B+)
/Display_3/DPIN3_D2-: DP_IN9.9 (D2-), S6.34 (D2_B-)
/Display_3/DPIN3_D3+: DP_IN9.10 (D3+), S6.32 (D3_B+)
/Display_3/DPIN3_D3-: DP_IN9.12 (D3-), S6.31 (D3_B-)
/Display_3/DPIN3_GND: D3.1 (K), DP_IN9.16 (GND4)
/Display_3/DPIN3_HPD: DP_IN9.18 (HPD), S6.17 (HPD_B)
/Display_3/DPIN3_PWR: DP_IN9.20 (PWR), R3.1
/Display_3/DPOUT_AUX+: DP_OUT3.15 (AUX+), S6.13 (AUX_C+)
/Display_3/DPOUT_AUX-: DP_OUT3.17 (AUX-), S6.14 (AUX_C-)
/Display_3/DPOUT_D0+: DP_OUT3.1 (D0+), S6.2 (D0_C+)
/Display_3/DPOUT_D0-: DP_OUT3.3 (D0-), S6.3 (D0_C-)
/Display_3/DPOUT_D1+: DP_OUT3.4 (D1+), S6.5 (D1_C+)
/Display_3/DPOUT_D1-: DP_OUT3.6 (D1-), S6.6 (D1_C-)
/Display_3/DPOUT_D2+: DP_OUT3.7 (D2+), S6.8 (D2_C+)
/Display_3/DPOUT_D2-: DP_OUT3.9 (D2-), S6.9 (D2_C-)
/Display_3/DPOUT_D3+: DP_OUT3.10 (D3+), S6.11 (D3_C+)
/Display_3/DPOUT_D3-: DP_OUT3.12 (D3-), S6.12 (D3_C-)
/Display_3/DPOUT_HPD: DP_OUT3.18 (HPD), S6.15 (HPD_C)
/Power Supply/VCC_IN: D11.1 (K), D12.1 (K), D13.1 (K), U6.3 (VI)
/S0: S1.1 (AUX_SEL), S1.56 (DX_SEL), S3.1 (AUX_SEL), S3.56 (DX_SEL), S5.1 (AUX_SEL), S5.56 (DX_SEL), S8.1 (AUX_SEL), S8.56 (DX_SEL), U5.15 (Q0)
/S1: S2.1 (AUX_SEL), S2.56 (DX_SEL), S4.1 (AUX_SEL), S4.56 (DX_SEL), S6.1 (AUX_SEL), S6.56 (DX_SEL), S7.1 (AUX_SEL), S7.56 (DX_SEL), U5.14 (Q1)
/USB Switch/+5V: S7.19 (VDD0), S7.43 (OE), S7.55 (VDD1), S8.19 (VDD0), S8.43 (OE), S8.55 (VDD1)
/USB Switch/D0+: S7.2 (D0_C+), USB1.3 (D+)
/USB Switch/D0-: S7.3 (D0_C-), USB1.2 (D-)
/USB Switch/D1+: S7.5 (D1_C+), USB1.6 (SSRX+)
/USB Switch/D1-: S7.6 (D1_C-), USB1.5 (SSRX-)
/USB Switch/D2+: S7.8 (D2_C+), USB1.9 (SSTX+)
/USB Switch/D2-: S7.9 (D2_C-), USB1.8 (SSTX-)
/USB Switch/USB_AB_D0+: S7.54 (D0_A+), S8.2 (D0_C+)
/USB Switch/USB_AB_D0-: S7.53 (D0_A-), S8.3 (D0_C-)
/USB Switch/USB_AB_D1+: S7.51 (D1_A+), S8.5 (D1_C+)
/USB Switch/USB_AB_D1-: S7.50 (D1_A-), S8.6 (D1_C-)
/USB Switch/USB_AB_D2+: S7.48 (D2_A+), S8.8 (D2_C+)
/USB Switch/USB_AB_D2-: S7.47 (D2_A-), S8.9 (D2_C-)
/USB Switch/USB_A_D0+: S8.54 (D0_A+), USB2.3 (D+)
/USB Switch/USB_A_D0-: S8.53 (D0_A-), USB2.2 (D-)
/USB Switch/USB_A_D1+: S8.51 (D1_A+), USB2.6 (SSRX+)
/USB Switch/USB_A_D1-: S8.50 (D1_A-), USB2.5 (SSRX-)
/USB Switch/USB_A_D2+: S8.48 (D2_A+), USB2.9 (SSTX+)
/USB Switch/USB_A_D2-: S8.47 (D2_A-), USB2.8 (SSTX-)
/USB Switch/USB_B_D0+: S8.41 (D0_B+), USB3.3 (D+)
/USB Switch/USB_B_D0-: S8.40 (D0_B-), USB3.2 (D-)
/USB Switch/USB_B_D1+: S8.38 (D1_B+), USB3.6 (SSRX+)
/USB Switch/USB_B_D1-: S8.37 (D1_B-), USB3.5 (SSRX-)
/USB Switch/USB_B_D2+: S8.35 (D2_B+), USB3.9 (SSTX+)
/USB Switch/USB_B_D2-: S8.34 (D2_B-), USB3.8 (SSTX-)
/USB Switch/USB_C_D0-: S7.40 (D0_B-), USB4.2 (D-)
/USB Switch/USB_C_D1+: S7.38 (D1_B+), USB4.6 (SSRX+)
/USB Switch/USB_C_D1-: S7.37 (D1_B-), USB4.5 (SSRX-)
/USB Switch/USB_C_D2+: S7.35 (D2_B+), USB4.9 (SSTX+)
/USB Switch/USB_C_D2-: S7.34 (D2_B-), USB4.8 (SSTX-)
GND: D6.1 (K), D7.1 (K), D8.1 (K), DP_IN1.2 (GND0), DP_IN1.5 (GND1), DP_IN1.8 (GND2), DP_IN1.11 (GND3), DP_IN1.13 (CON1), DP_IN1.14 (CON2), DP_IN1.16 (GND4), DP_IN2.2 (GND0), DP_IN2.5 (GND1), DP_IN2.8 (GND2), DP_IN2.11 (GND3), DP_IN2.13 (CON1), DP_IN2.14 (CON2), DP_IN2.16 (GND4), DP_IN4.2 (GND0), DP_IN4.5 (GND1), DP_IN4.8 (GND2), DP_IN4.11 (GND3), DP_IN4.13 (CON1), DP_IN4.14 (CON2), DP_IN4.16 (GND4), DP_IN5.2 (GND0), DP_IN5.5 (GND1), DP_IN5.8 (GND2), DP_IN5.11 (GND3), DP_IN5.13 (CON1), DP_IN5.14 (CON2), DP_IN5.16 (GND4), DP_IN7.2 (GND0), DP_IN7.5 (GND1), DP_IN7.8 (GND2), DP_IN7.11 (GND3), DP_IN7.13 (CON1), DP_IN7.14 (CON2), DP_IN7.16 (GND4), DP_IN8.2 (GND0), DP_IN8.5 (GND1), DP_IN8.8 (GND2), DP_IN8.11 (GND3), DP_IN8.13 (CON1), DP_IN8.14 (CON2), DP_IN8.16 (GND4), DP_OUT1.2 (GND0), DP_OUT1.5 (GND1), DP_OUT1.8 (GND2), DP_OUT1.11 (GND3), DP_OUT1.13 (CON1), DP_OUT1.14 (CON2), DP_OUT1.16 (GND4), DP_OUT2.2 (GND0), DP_OUT2.5 (GND1), DP_OUT2.8 (GND2), DP_OUT2.11 (GND3), DP_OUT2.13 (CON1), DP_OUT2.14 (CON2), DP_OUT2.16 (GND4), DP_OUT3.2 (GND0), DP_OUT3.5 (GND1), DP_OUT3.8 (GND2), DP_OUT3.11 (GND3), DP_OUT3.13 (CON1), DP_OUT3.14 (CON2), DP_OUT3.16 (GND4), J1.2, J1.3, PWR1.2, PWR2.2, PWR2.3, PWR3.4 (GND), PWR3.5 (Shield), S1.4 (GND0), S1.7 (GND1), S1.10 (GND2), S1.33 (GND3), S1.36 (GND4), S1.39 (GND5), S1.46 (GND6), S1.49 (GND7), S1.52 (GND8), S2.4 (GND0), S2.7 (GND1), S2.10 (GND2), S2.33 (GND3), S2.36 (GND4), S2.39 (GND5), S2.46 (GND6), S2.49 (GND7), S2.52 (GND8), S3.4 (GND0), S3.7 (GND1), S3.10 (GND2), S3.33 (GND3), S3.36 (GND4), S3.39 (GND5), S3.46 (GND6), S3.49 (GND7), S3.52 (GND8), S4.4 (GND0), S4.7 (GND1), S4.10 (GND2), S4.33 (GND3), S4.36 (GND4), S4.39 (GND5), S4.46 (GND6), S4.49 (GND7), S4.52 (GND8), S5.4 (GND0), S5.7 (GND1), S5.10 (GND2), S5.33 (GND3), S5.36 (GND4), S5.39 (GND5), S5.46 (GND6), S5.49 (GND7), S5.52 (GND8), S6.4 (GND0), S6.7 (GND1), S6.10 (GND2), S6.33 (GND3), S6.36 (GND4), S6.39 (GND5), S6.46 (GND6), S6.49 (GND7), S6.52 (GND8), S7.4 (GND0), S7.7 (GND1), S7.10 (GND2), S7.33 (GND3), S7.36 (GND4), S7.39 (GND5), S7.46 (GND6), S7.49 (GND7), S7.52 (GND8), S8.4 (GND0), S8.7 (GND1), S8.10 (GND2), S8.33 (GND3), S8.36 (GND4), S8.39 (GND5), S8.46 (GND6), S8.49 (GND7), S8.52 (GND8), U3.8 (VSS), U5.8 (GND), U6.1 (GND), USB1.4 (GND), USB1.7 (GND_DRAIN)
unnamed: D1.2 (A), R1.2
unnamed: D2.2 (A), R2.2
unnamed: D3.2 (A), R3.2
unnamed: D6.2 (A), R4.2
unnamed: D7.2 (A), R5.2
unnamed: D8.2 (A), R6.2
unnamed: D11.2 (A), PWR2.1
unnamed: D12.2 (A), PWR3.1 (VBUS)
unnamed: D13.2 (A), PWR1.1
unnamed: S1.13 (AUX_C+), S2.30 (AUX_A+)
unnamed: S1.14 (AUX_C-), S2.29 (AUX_A-)
unnamed: S1.2 (D0_C+), S2.54 (D0_A+)
unnamed: S1.3 (D0_C-), S2.53 (D0_A-)
unnamed: S1.5 (D1_C+), S2.51 (D1_A+)
unnamed: S1.6 (D1_C-), S2.50 (D1_A-)
unnamed: S1.8 (D2_C+), S2.48 (D2_A+)
unnamed: S1.9 (D2_C-), S2.47 (D2_A-)
unnamed: S1.11 (D3_C+), S2.45 (D3_A+)
unnamed: S1.12 (D3_C-), S2.44 (D3_A-)
unnamed: S1.15 (HPD_C), S2.16 (HPD_A)
unnamed: S3.13 (AUX_C+), S4.30 (AUX_A+)
unnamed: S3.14 (AUX_C-), S4.29 (AUX_A-)
unnamed: S3.2 (D0_C+), S4.54 (D0_A+)
unnamed: S3.3 (D0_C-), S4.53 (D0_A-)
unnamed: S3.5 (D1_C+), S4.51 (D1_A+)
unnamed: S3.6 (D1_C-), S4.50 (D1_A-)
unnamed: S3.8 (D2_C+), S4.48 (D2_A+)
unnamed: S3.9 (D2_C-), S4.47 (D2_A-)
unnamed: S3.11 (D3_C+), S4.45 (D3_A+)
unnamed: S3.12 (D3_C-), S4.44 (D3_A-)
unnamed: S3.15 (HPD_C), S4.16 (HPD_A)
unnamed: S5.13 (AUX_C+), S6.30 (AUX_A+)
unnamed: S5.14 (AUX_C-), S6.29 (AUX_A-)
unnamed: S5.2 (D0_C+), S6.54 (D0_A+)
unnamed: S5.3 (D0_C-), S6.53 (D0_A-)
unnamed: S5.5 (D1_C+), S6.51 (D1_A+)
unnamed: S5.6 (D1_C-), S6.50 (D1_A-)
unnamed: S5.8 (D2_C+), S6.48 (D2_A+)
unnamed: S5.9 (D2_C-), S6.47 (D2_A-)
unnamed: S5.11 (D3_C+), S6.45 (D3_A+)
unnamed: S5.12 (D3_C-), S6.44 (D3_A-)
unnamed: S5.15 (HPD_C), S6.16 (HPD_A)

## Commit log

2023-09-01 Add projects
2023-09-01 Update docs
2023-09-01 Melhorias no módulo controlador
